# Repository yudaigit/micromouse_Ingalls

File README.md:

# Micromouse "Ingalls"
Contains micromouse specification, code, and list of items.

# Table of Contents
1. Introduction
2. Design Goals
3. Schematic diagram
4. Parts List
5. Codes

# 1. Introduction
**Micromouse** : A maze-solving robot with wall sensors and electric motor.

**Expected specification of this mouse**
- Motor: Stepping Motor (for ease of coding)
- Microcontroller: ESP32
- Wall detection: IR LED + suitable phototransistor
- Wheels: 2 wheels + sheet with smooth surface in front
- Battery: Lipo battery (12V)
- Maze-solving algorism Adachi method
- Chassis would be made out of circuit board. 

**Important Regulation** 
- Mouse must fit on 18cm x 18cm unit square.
- Each run that in which the mouse successfully reaches the goal is given a run time.
- Shortest time out of all runs is considered the official record. 
- 10 minutes limit including adjusting parameters.
- No limit on the number of runs
Regulation found here [2024 IEEE MIT Micromouse Guideline.pdf](https://github.com/user-attachments/files/17085412/2024.IEEE.MIT.Micromouse.Guideline.pdf)

Picture from Wikipedia [Link](https://en.wikipedia.org/wiki/Micromouse)

# 2. Design Goals
Design of this mouse is referred to Beginner Mouse V2 by Micromouse Hokuriku Dokokai. 

Website Link: [Click here](https://sites.google.com/a/itolab-ktc.com/mouse_hokuriku/basicmouse2) 
Website in Japanese so needs Google Translation

Picture from linked website by Micromouse Hokuriku Dokokai

**Changes to be made:**
- Microcontroller changed from RX220 to ESP32S3-devkit
- IR LED and Photo-transistor changed due to item availablity in the US
- Wheels will be 3D printed using resin printer.
- Further modification expected.

# 3. Schematic Diagram
Schematic diagram is contained in this repository in KICAD format.
Detailed explanation of each component is found in this Google Slides. [Link: Slides](https://docs.google.com/presentation/d/1O1cH-XDseA_9v0i9zR2N1KNmGXuSQ24eQ0dWm67MaV0/edit?usp=sharing)

# 4. Parts List
| Parts Name | Part Number | Website | Explanation |
| ---------- | ----------- | ------- | ----------- |
| Microcontroller | ESP32-S3-DEVKITC-1-N8R8 | [Link: Digikey](https://www.digikey.com/en/products/detail/espressif-systems/ESP32-S3-DEVKITC-1-N8R8/15295894?so=88713219&content=productdetail_US&mkt_tok=MDI4LVNYSy01MDcAAAGVjI7rAclhlAR_R00akBj8bqdP8uLlM8oDSYOZye-3bv9ezUbQ4VchOdj5mMELOEFJc6lgwUlzkdWoqtAFwKCPgx3IHGqwjkK5CxoQCtvj) | Devkit includes USB-UART bridge, Reset/Boot-mode bottons, LDO regulator, micro-USB connector. |
| Motor Driver  | A3982SLBTR-T | [Link: Digikey](https://www.digikey.com/en/products/detail/allegro-microsystems/A3982SLBTR-T/1006337?so=88713219&content=productdetail_US&mkt_tok=MDI4LVNYSy01MDcAAAGVjI7rAXo1NKZFh-lfgPb5J_lPGqp54pRkpawmU758xRtKlHEaEAZEIfTsmPXZYi-8XfwW9QOW9wnnimUpZHAQ6QVG9tBGOJKe-bg7pqzY) | Output drive capacity of up to 35 V and ±2 A |
| Transistor Array  | TBD62083AFNG,EL  | [Link: Digikey](https://www.digikey.com/en/products/detail/toshiba-semiconductor-and-storage/TBD62083AFNG-EL/5514101?so=88713219&content=productdetail_US&mkt_tok=MDI4LVNYSy01MDcAAAGVjI7rASWC-GBVGhXV-_J2TC-AzhnJu9-OEVNVk5YSU11mHZzysy7OMH7-JYZRrl2jqi5ujeSUjEmdH1xTrglv5ZYsNYvOeUH_rRTn88Kt) |
| IR LED | SFH 4545 | [Link: Digikey](https://www.digikey.com/en/products/detail/ams-osram-usa-inc/SFH-4545/2205955?so=88714059&content=productdetail_US&mkt_tok=MDI4LVNYSy01MDcAAAGVjRuHY0UsPo8PqHZpcf0OJ5lFMERFDRTdYCMr3sMDzpaXmtWfPRvpUV_ZyHRayo5sOlhpeXiFwpQmKslB2cN6vLcBioWK0pLHrexKfSO7) | Peak Wavelength of 950nm. |
| Phototransistor | TEFT4300 | [Link: Digikey](https://www.digikey.com/en/products/detail/vishay-semiconductor-opto-division/TEFT4300/1681175?so=88714059&content=productdetail_US&mkt_tok=MDI4LVNYSy01MDcAAAGVjRuHY_XwD63POgCk77Uz4CcDU6UOm_5Ec3PsV4QUbsIlVZEZImGF-MNmtf094ZbBvAZZl5DjMfcmu5q6gha0bCU4jfj_RwPxrJv7J39u) | Full performance at wavelength of 940nm |
| Motor | PKP213D05A | [Link: MISUMI](https://us.misumi-ec.com/vona2/detail/221004949472/?HissuCode=PKP213D05A) | Rated Voltage of 4.25V and rated current of 0.5A |
| Regulator | NJM2845DL1-05 | [Link: MOUSER](https://www.mouser.com/ProductDetail/Nisshinbo/NJM2845DL1-05-TE1?qs=Vf9KeiGtj%252BGbfCGSGlajaA%3D%3D&countryCode=US&currencyCode=USD) | Converts 12V to 5V |
| Regulator | NJM2845DL1-33 | [Link: MOUSER](https://www.mouser.com/ProductDetail/Nisshinbo/NJM2845DL1-33-TE1?qs=Vf9KeiGtj%252BHsxdmME1E7bA%3D%3D&countryCode=US&currencyCode=USD) | Converts 5V to 3.3V |
| Variable Resistor | 3362P-1-103LF | [Link: MOUSER](https://www.mouser.com/ProductDetail/Bourns/3362P-1-103LF?qs=tS7CBNq%252BQ07BavGNEQud%252BA%3D%3D&countryCode=US&currencyCode=USD) |

# 5. Codes
Codes were taken and based on Pi:Co V2 Micromouse developed by RT.corp.
Github repo for Pi:Co V2 is found here. [Link](https://github.com/rt-net/pico_v2_arduino_examples)

Explanation of code V1:
- Codes are mostly similar to the one made for Pi:Co V2.
- Some codes were added for better performance, including slalom, hardware correction and wall-cut correction.
- Instead of pushing the button to start, it starts when you wipe a hand in front of the wall-sensor.
- All values were taken for half-size micromouse. For this competition, they must be changed.

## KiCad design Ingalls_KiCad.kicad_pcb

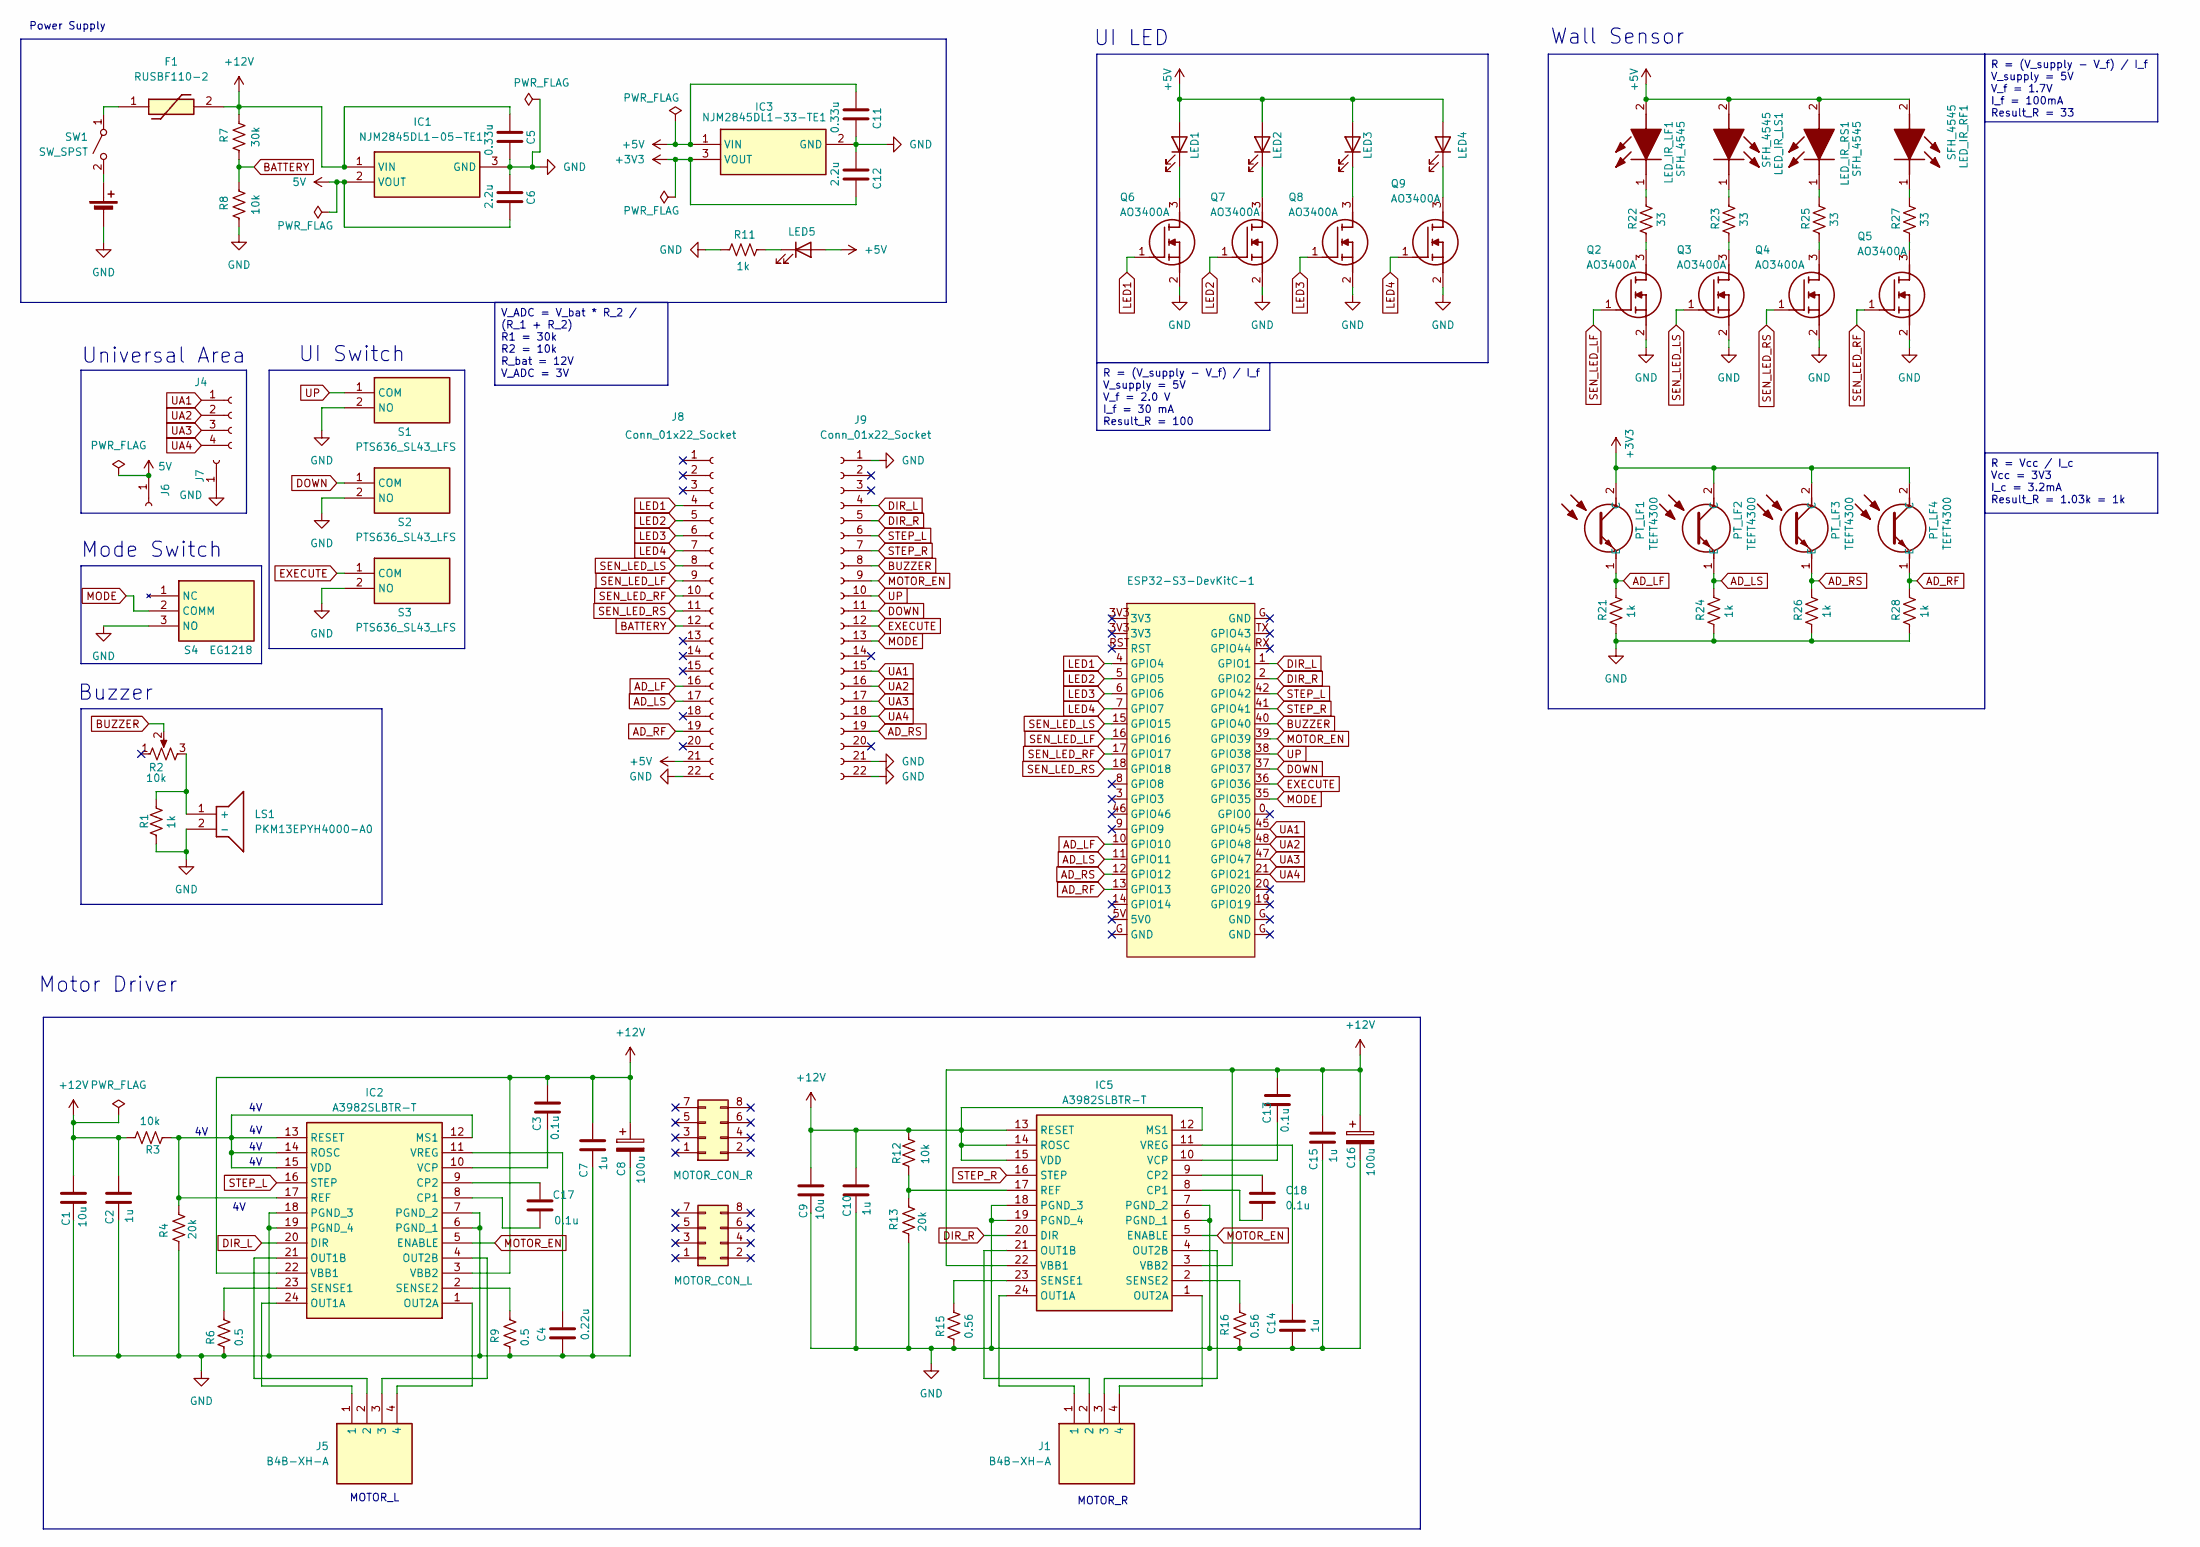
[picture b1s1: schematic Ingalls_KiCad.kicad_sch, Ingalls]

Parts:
BT1: Battery_Cell; PinHeader_1x02_P1.27mm_Vertical
C1, C9: 10u; C_0603_1608Metric
C2, C7, C10, C14, C15: 1u; C_0603_1608Metric
C3, C13, C17, C18: 0.1u; C_0603_1608Metric
C4: 0.22u; C_0603_1608Metric
C5, C11: 0.33u; C_0603_1608Metric
C6, C12: 2.2u; C_0603_1608Metric
C8, C16: 100u; PCAP_SEP_C6_PAN
D1: LED5; LED_D5.0mm
ESP32-S3-DevKitC-1: (no value)
F1: RUSBF110-2; RUSBF1102; Manufacturer_Part_Number RUSBF110-2; Mouser Part Number 650-RUSBF110-2
IC1: NJM2845DL1-05-TE1; TO-252-3-L1; Manufacturer_Part_Number NJM2845DL1-05-TE1; Mouser Part Number 513-NJM2845DL105-TE1
IC2, IC5: A3982SLBTR-T; A3959SLBTRT; Manufacturer_Part_Number A3982SLBTR-T; Mouser Part Number 250-A3982SLBTR-T
IC3: NJM2845DL1-33-TE1; NJM2845DL133TE1; Manufacturer_Part_Number NJM2845DL1-33-TE1; Mouser Part Number 513-NJM2845DL133-TE1
J1, J5: B4B-XH-A; B4BXHA; Manufacturer_Part_Number B4B-XH-A
J2: MOTOR_CON_R
J3: MOTOR_CON_L
J4: Conn_01x04_Socket; PinHeader_1x04_P2.54mm_Vertical
J6, J7: Conn_01x01_Socket; PinSocket_1x01_P2.54mm_Vertical
J8, J9: Conn_01x22_Socket; PinSocket_1x22_P2.54mm_Vertical
LED1, LED2, LED3, LED4: LED; LED_D5.0mm
LED_IR_LF1: SFH_4545; SFH4545; Mouser Part Number 720-SFH4545
LED_IR_LS1: SFH_4545; SFH4545; Mouser Part Number 720-SFH4545
LED_IR_RF1: SFH_4545; SFH4545; Mouser Part Number 720-SFH4545
LED_IR_RS1: SFH_4545; SFH4545; Mouser Part Number 720-SFH4545
LS1: PKM13EPYH4000-A0; PKM13EPYH4000A0; Manufacturer_Part_Number PKM13EPYH4000-A0; Mouser Part Number 81-PKM13EPYH4000-A0
PT_LF1, PT_LF2, PT_LF3, PT_LF4: TEFT4300; Manufacturer_Part_Number TEFT4300; Mouser Part Number 782-TEFT4300
Q2, Q3, Q4, Q5, Q6, Q7, Q8, Q9: AO3400A; SOT95P280X125-3N; Manufacturer_Part_Number AO3400A
R1, R11, R21, R24, R26, R28: 1k; R_0603_1608Metric
R2: 10k; 3362P_1
R3, R8, R12: 10k; R_0603_1608Metric
R4, R13: 20k; R_0603_1608Metric
R6, R9: 0.5; R_2512_6332Metric
R7: 30k; R_0603_1608Metric
R15, R16: 0.56; R_2512_6332Metric
R22, R23, R25, R27: 33; R_0603_1608Metric
S1, S2, S3: PTS636_SL43_LFS; PTS636SL43LFS; Manufacturer_Part_Number PTS636 SL43 LFS; Mouser Part Number 611-PTS636SL43LFS
S4: EG1218; SW_1218_EWI; Manufacturer_Part_Number EG1218; Mouser Part Number 612-EG1218
SW1: SW_SPST; ANT11SF1CQE

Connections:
5V: C6.1, IC1.2 (VOUT), J6.1
+3V3: C12.1, IC3.3 (VOUT), PT_LF1.2 (C), PT_LF2.2 (C), PT_LF3.2 (C), PT_LF4.2 (C)
+5V: C11.2, D1.2 (A), IC3.1 (VIN), J8.21, LED1.2 (A), LED2.2 (A), LED3.2 (A), LED4.2 (A), LED_IR_LF1.2 (A), LED_IR_LS1.2 (A), LED_IR_RF1.2 (A), LED_IR_RS1.2 (A)
+12V: C1.1, C2.1, C3.1, C5.2, C7.1, C8.1, C9.1, C10.1, C13.1, C15.1, C16.1, F1.2, IC1.1 (VIN), IC2.3 (VBB2), IC2.22 (VBB1), IC5.3 (VBB2), IC5.12 (MS1), IC5.13 (RESET), IC5.14 (ROSC), IC5.15 (VDD), IC5.22 (VBB1), R3.1, R7.2, R12.1
AD_LF: ESP32-S3-DevKitC-1.10 (GPIO10), J8.16, PT_LF1.1 (E), R21.1
AD_LS: ESP32-S3-DevKitC-1.11 (GPIO11), J8.17, PT_LF2.1 (E), R24.1
AD_RF: ESP32-S3-DevKitC-1.13 (GPIO13), J8.19, PT_LF4.1 (E), R28.1
AD_RS: ESP32-S3-DevKitC-1.12 (GPIO12), J9.19, PT_LF3.1 (E), R26.1
BATTERY: J8.12, R7.1, R8.2
BUZZER: ESP32-S3-DevKitC-1.40 (GPIO40), J9.8, R2.2
DIR_L: ESP32-S3-DevKitC-1.1 (GPIO1), IC2.20 (DIR), J9.4
DIR_R: ESP32-S3-DevKitC-1.2 (GPIO2), IC5.20 (DIR), J9.5
DOWN: ESP32-S3-DevKitC-1.37 (GPIO37), J9.11, S2.1 (COM)
EXECUTE: ESP32-S3-DevKitC-1.36 (GPIO36), J9.12, S3.1 (COM)
GND: BT1.2 (-), C1.2, C2.2, C4.2, C5.1, C6.2, C7.2, C8.2, C9.2, C10.2, C11.1, C12.2, C14.2, C15.2, C16.2, IC1.3 (GND), IC2.6 (PGND_1), IC2.7 (PGND_2), IC2.18 (PGND_3), IC2.19 (PGND_4), IC3.2 (GND), IC5.6 (PGND_1), IC5.7 (PGND_2), IC5.18 (PGND_3), IC5.19 (PGND_4), J7.1, J8.22, J9.1, J9.21, J9.22, LS1.2 (-), Q2.2 (S), Q3.2 (S), Q4.2 (S), Q5.2 (S), Q6.2 (S), Q7.2 (S), Q8.2 (S), Q9.2 (S), R1.2, R4.2, R6.2, R8.1, R9.2, R11.1, R13.2, R15.2, R16.2, R21.2, R24.2, R26.2, R28.2, S1.2 (NO), S2.2 (NO), S3.2 (NO), S4.3 (NO)
LED1: ESP32-S3-DevKitC-1.4 (GPIO4), J8.4, Q6.1 (G)
LED2: ESP32-S3-DevKitC-1.5 (GPIO5), J8.5, Q7.1 (G)
LED3: ESP32-S3-DevKitC-1.6 (GPIO6), J8.6, Q8.1 (G)
LED4: ESP32-S3-DevKitC-1.7 (GPIO7), J8.7, Q9.1 (G)
MODE: ESP32-S3-DevKitC-1.35 (GPIO35), J9.13, S4.2 (COMM)
MOTOR_EN: ESP32-S3-DevKitC-1.39 (GPIO39), IC2.5 (ENABLE), IC5.5 (ENABLE), J9.9
unnamed: BT1.1 (+), SW1.2 (B)
unnamed: D1.1 (K), R11.2
unnamed: C17.2, IC2.8 (CP1)
unnamed: C17.1, IC2.9 (CP2)
unnamed: IC2.12 (MS1), IC2.13 (RESET), IC2.14 (ROSC), IC2.15 (VDD), IC2.17 (REF), R3.2, R4.1
unnamed: IC2.24 (OUT1A), J5.1
unnamed: IC2.21 (OUT1B), J5.2
unnamed: IC2.1 (OUT2A), J5.4
unnamed: IC2.4 (OUT2B), J5.3
unnamed: IC2.23 (SENSE1), R6.1
unnamed: IC2.2 (SENSE2), R9.1
unnamed: C3.2, IC2.10 (VCP)
unnamed: C4.1, IC2.11 (VREG)
unnamed: C18.2, IC5.8 (CP1)
unnamed: C18.1, IC5.9 (CP2)
unnamed: IC5.24 (OUT1A), J1.1
unnamed: IC5.21 (OUT1B), J1.2
unnamed: IC5.1 (OUT2A), J1.4
unnamed: IC5.4 (OUT2B), J1.3
unnamed: IC5.17 (REF), R12.2, R13.1
unnamed: IC5.23 (SENSE1), R15.1
unnamed: IC5.2 (SENSE2), R16.1
unnamed: C13.2, IC5.10 (VCP)
unnamed: C14.1, IC5.11 (VREG)
unnamed: LED1.1 (K), Q6.3 (D)
unnamed: LED2.1 (K), Q7.3 (D)
unnamed: LED3.1 (K), Q8.3 (D)
unnamed: LED4.1 (K), Q9.3 (D)
unnamed: LED_IR_LF1.1 (K), R22.1
unnamed: LED_IR_LS1.1 (K), R23.1
unnamed: LED_IR_RF1.1 (K), R27.1
unnamed: LED_IR_RS1.1 (K), R25.1
unnamed: LS1.1 (+), R1.1, R2.3
unnamed: Q2.3 (D), R22.2
unnamed: Q3.3 (D), R23.2
unnamed: Q4.3 (D), R25.2
unnamed: Q5.3 (D), R27.2
unnamed: F1.1, SW1.1 (A)
SEN_LED_LF: ESP32-S3-DevKitC-1.16 (GPIO16), J8.9, Q2.1 (G)
SEN_LED_LS: ESP32-S3-DevKitC-1.15 (GPIO15), J8.8, Q3.1 (G)
SEN_LED_RF: ESP32-S3-DevKitC-1.17 (GPIO17), J8.10, Q5.1 (G)
SEN_LED_RS: ESP32-S3-DevKitC-1.18 (GPIO18), J8.11, Q4.1 (G)
STEP_L: ESP32-S3-DevKitC-1.42 (GPIO42), IC2.16 (STEP), J9.6
STEP_R: ESP32-S3-DevKitC-1.41 (GPIO41), IC5.16 (STEP), J9.7
UA1: ESP32-S3-DevKitC-1.45 (GPIO45), J4.1, J9.15
UA2: ESP32-S3-DevKitC-1.48 (GPIO48), J4.2, J9.16
UA3: ESP32-S3-DevKitC-1.47 (GPIO47), J4.3, J9.17
UA4: ESP32-S3-DevKitC-1.21 (GPIO21), J4.4, J9.18
UP: ESP32-S3-DevKitC-1.38 (GPIO38), J9.10, S1.1 (COM)

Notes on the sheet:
UI Switch
Buzzer
Mode Switch
Wall Sensor
Universal Area
MOTOR_L
MOTOR_R
Motor Driver
Power Supply
UI LED
R = (V_supply - V_f) / I_f V_supply = 5V V_f = 2.0 V I_f = 30 mA Result_R = 100
R = Vcc / I_c Vcc = 3V3 I_c = 3.2mA Result_R = 1.03k = 1k
V_ADC = V_bat * R_2 / (R_1 + R_2) R1 = 30k R2 = 10k R_bat = 12V V_ADC = 3V
R = (V_supply - V_f) / I_f V_supply = 5V V_f = 1.7V I_f = 100mA Result_R = 33

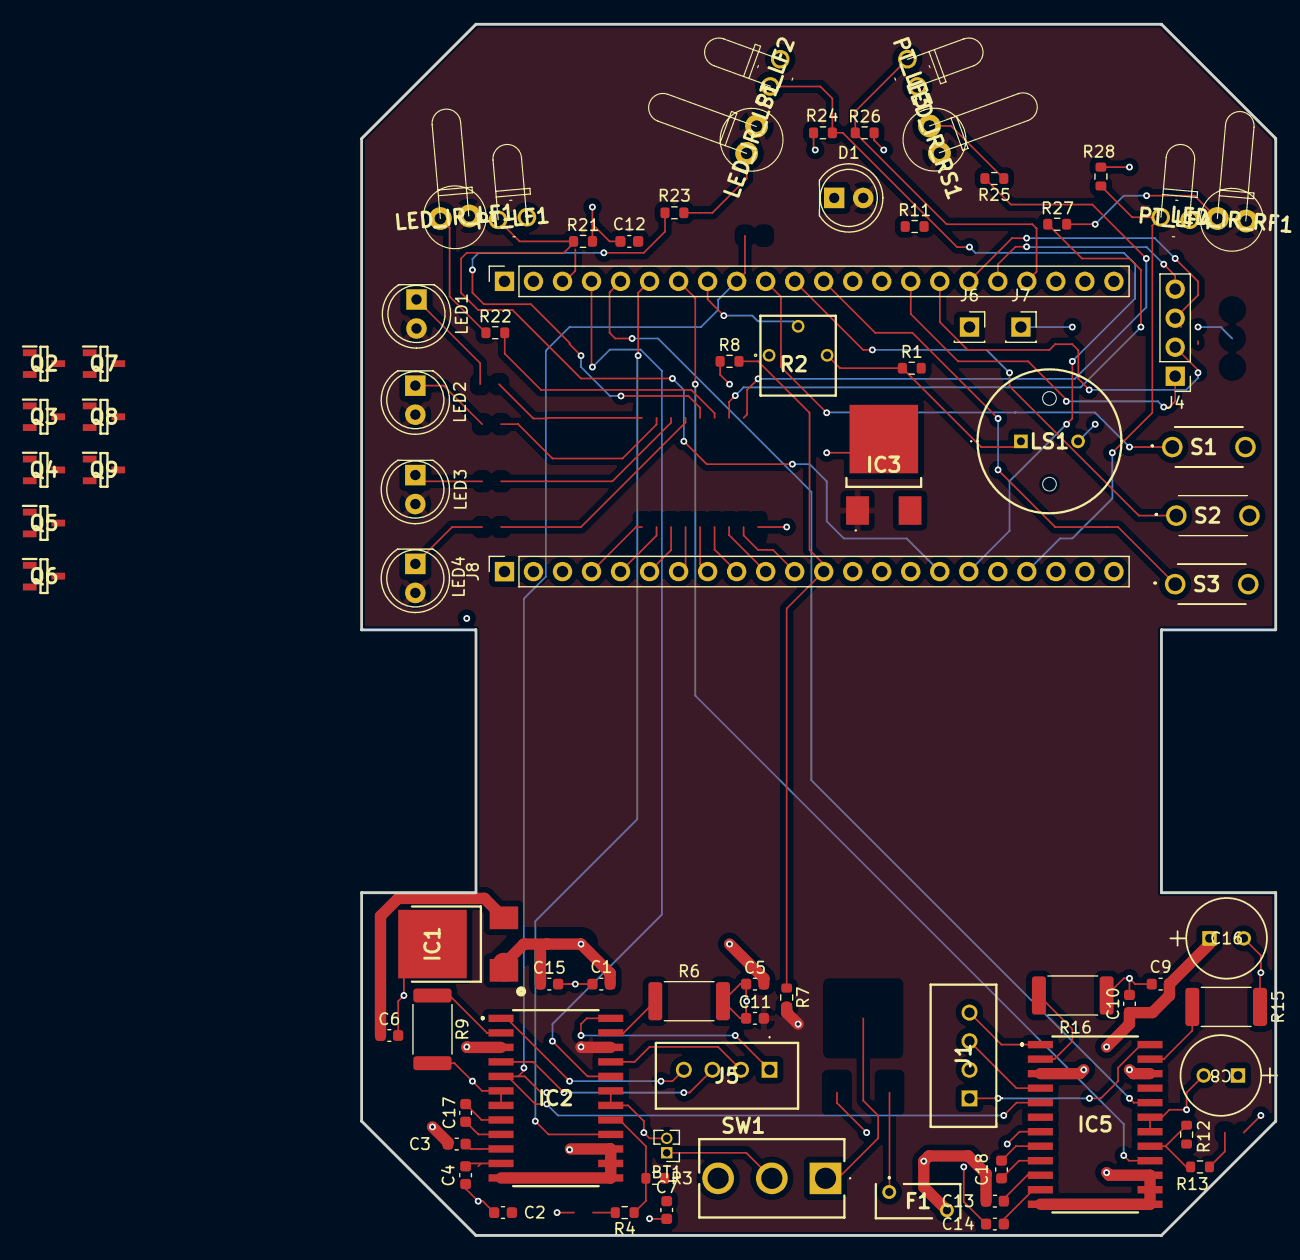
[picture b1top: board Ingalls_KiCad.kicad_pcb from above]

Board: 4 copper layers, 80.0 x 106.0 mm, 78 parts (0 on the bottom side), 69 nets.

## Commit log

2025-05-24 Added KiCAD file with one resister
2025-05-24 Previous KICAD progress sync
2025-05-24 Footprint Library added
2025-05-24 Footprint data changed
2025-05-24 Changes added
2025-05-24 Title added
2025-05-24 PCB updated
2025-05-30 Changed circuit around LED by replacing the multi-pin chip with MOSFET
2025-06-02 Changes made
